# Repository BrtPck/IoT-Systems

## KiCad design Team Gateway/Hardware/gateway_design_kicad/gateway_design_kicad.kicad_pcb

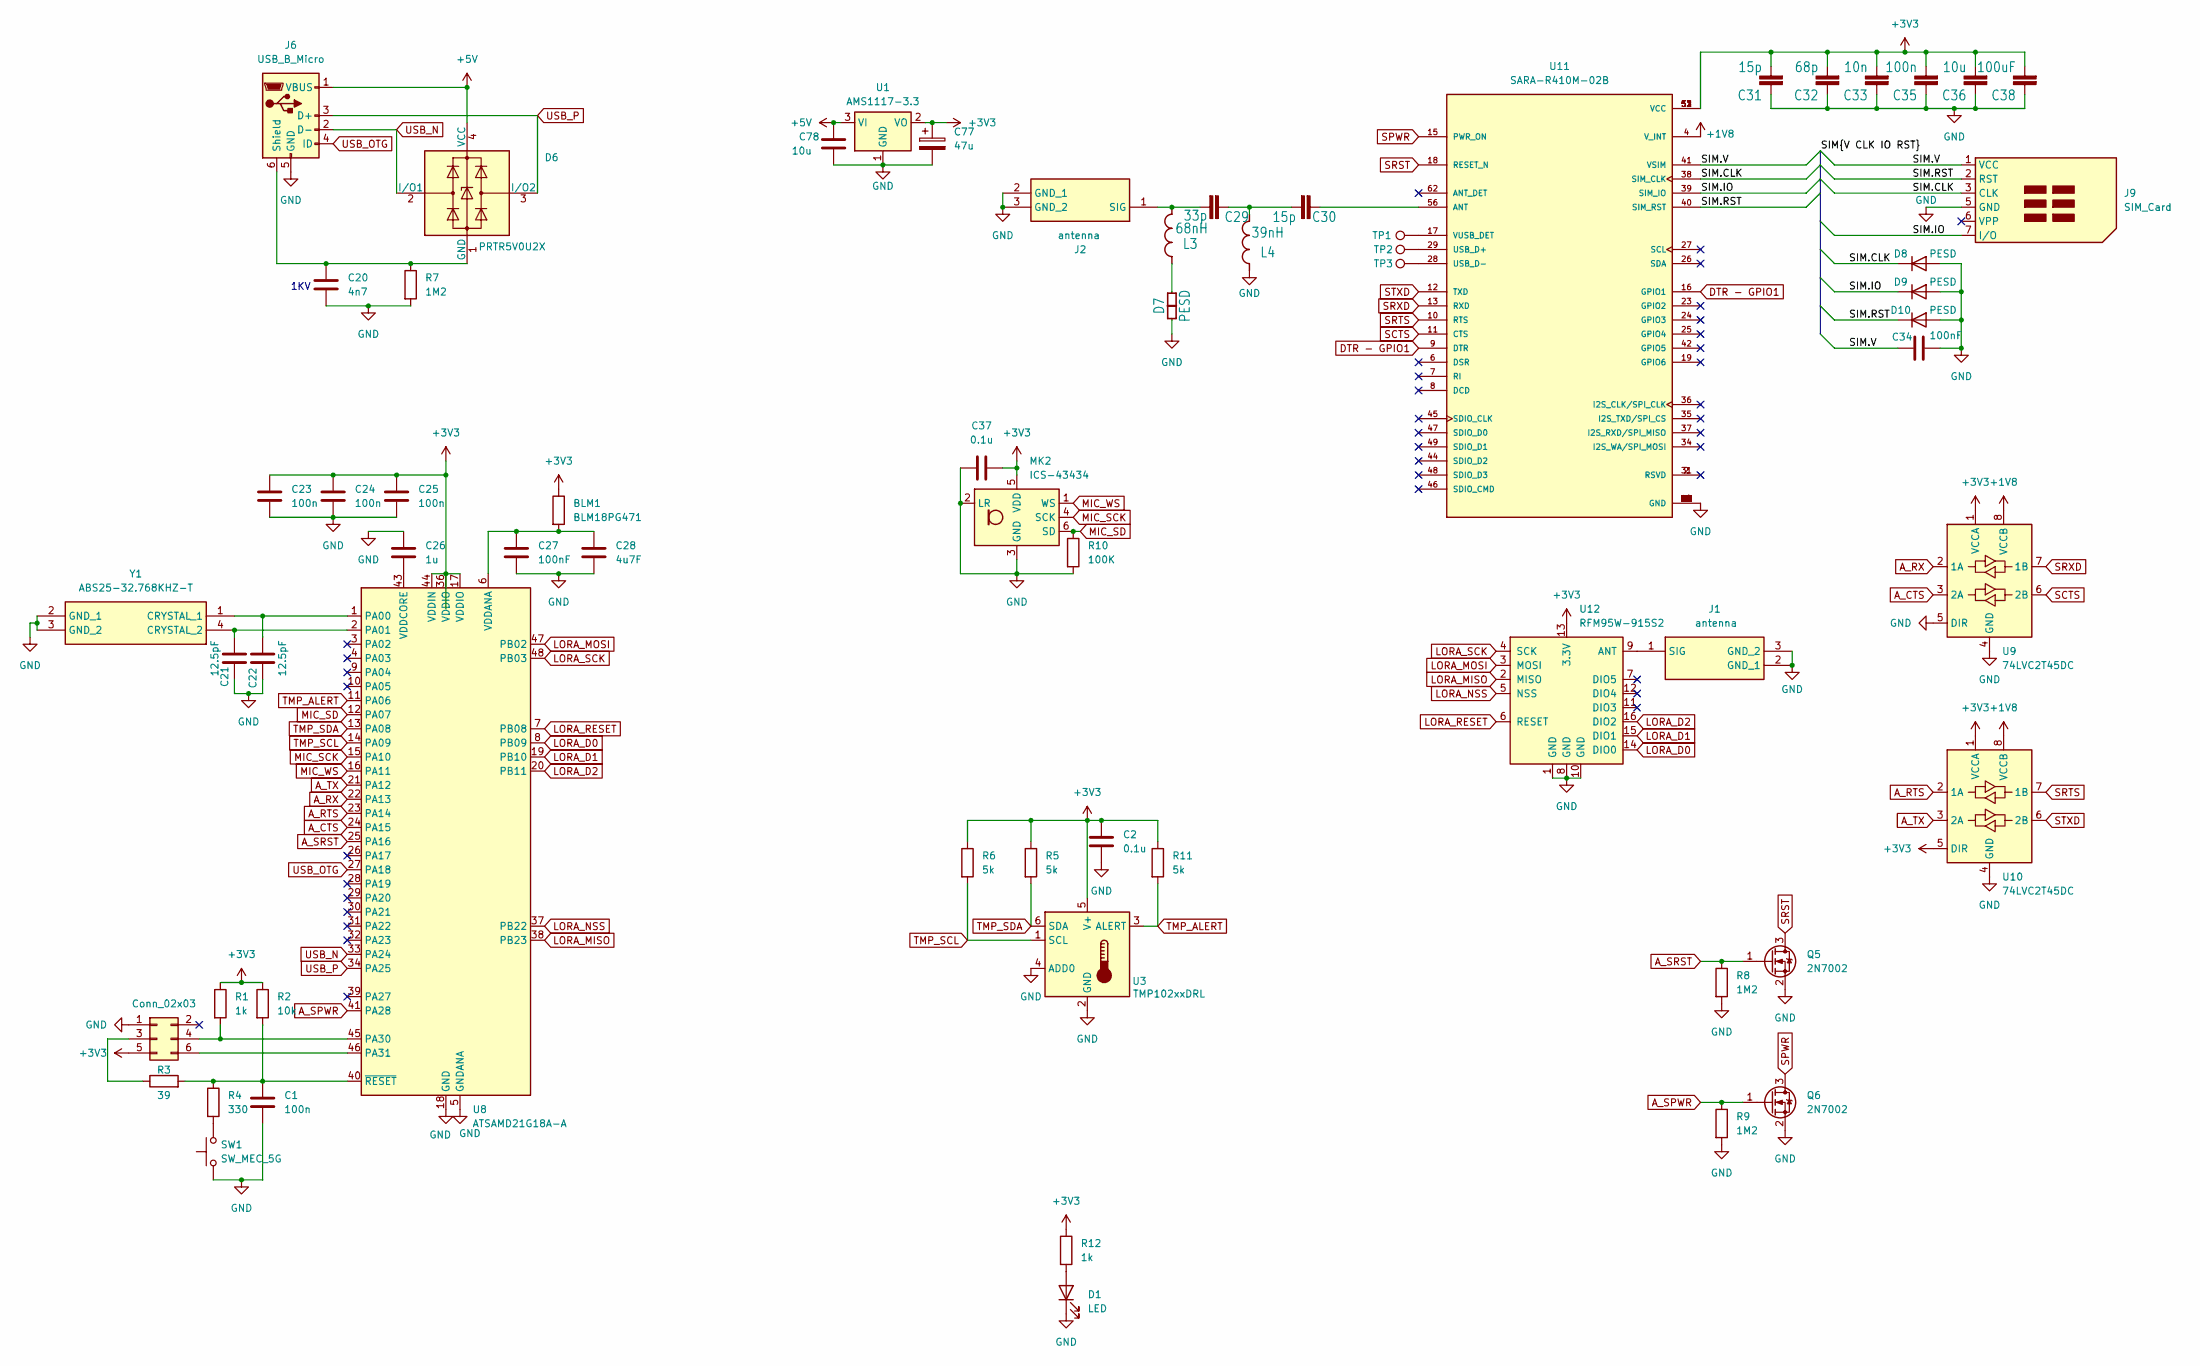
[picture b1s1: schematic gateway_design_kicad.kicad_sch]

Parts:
BLM1: BLM18PG471; C_0603_1608Metric_Pad1.08x0.95mm_HandSolder
C1, C23, C24, C25, C35: 100n; C_0805_2012Metric_Pad1.18x1.45mm_HandSolder
C2, C37: 0.1u; C_0805_2012Metric_Pad1.18x1.45mm_HandSolder
C20: 4n7; C_0805_2012Metric_Pad1.18x1.45mm_HandSolder
C21, C22: 12.5pF; C_0805_2012Metric_Pad1.18x1.45mm_HandSolder
C26: 1u; C_0805_2012Metric_Pad1.18x1.45mm_HandSolder
C27, C34: 100nF; C_0805_2012Metric_Pad1.18x1.45mm_HandSolder
C28: 4u7F; C_0805_2012Metric_Pad1.18x1.45mm_HandSolder
C29: 33p; C_0805_2012Metric_Pad1.18x1.45mm_HandSolder
C30, C31: 15p; C_0805_2012Metric_Pad1.18x1.45mm_HandSolder
C32: 68p; C_0805_2012Metric_Pad1.18x1.45mm_HandSolder
C33: 10n; C_0805_2012Metric_Pad1.18x1.45mm_HandSolder
C36, C78: 10u; C_0805_2012Metric_Pad1.18x1.45mm_HandSolder
C38: 100uF; C_0805_2012Metric_Pad1.18x1.45mm_HandSolder
C77: 47u; C_0805_2012Metric_Pad1.18x1.45mm_HandSolder
D1: LED; LED_0805_2012Metric_Pad1.15x1.40mm_HandSolder
D6: PRTR5V0U2X; SOT-143
D7, D8, D9, D10: PESD; eigen_PESD0402-140
J1, J2: antenna; Antenna; Mouser Part Number N/A
J6: USB_B_Micro; 21344412
J7: Conn_02x03; PinHeader_2x03_P2.54mm_Vertical
J9: SIM_Card; SIM5051601800A
L3: 68nH; C_0805_2012Metric_Pad1.18x1.45mm_HandSolder
L4: 39nH; C_0603_1608Metric_Pad1.08x0.95mm_HandSolder
MK2: ICS-43434; InvenSense_ICS-43434-6_3.5x2.65mm
Q5, Q6: 2N7002; SOT-23
R1, R12: 1k; R_0805_2012Metric_Pad1.20x1.40mm_HandSolder
R2: 10k; R_0805_2012Metric_Pad1.20x1.40mm_HandSolder
R3: 39; R_0805_2012Metric_Pad1.20x1.40mm_HandSolder
R4: 330; R_0805_2012Metric_Pad1.20x1.40mm_HandSolder
R5, R6, R11: 5k; R_0805_2012Metric_Pad1.20x1.40mm_HandSolder
R7, R8, R9: 1M2; R_0805_2012Metric_Pad1.20x1.40mm_HandSolder
R10: 100K; R_0805_2012Metric_Pad1.20x1.40mm_HandSolder
SW1: SW_MEC_5G; SW_DIP_SPSTx01_Slide_6.7x4.1mm_W6.73mm_P2.54mm_LowProfile_J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
TP1, TP2, TP3: TestPoint; TestPoint_Pad_2.0x2.0mm
U1: AMS1117-3.3; SOT-223-3_TabPin2
U3: TMP102xxDRL; SOT-563
U8: ATSAMD21G18A-A; TQFP-48_7x7mm_P0.5mm
U9, U10: 74LVC2T45DC; VSSOP-8_2.3x2mm_P0.5mm
U11: SARA-R410M-02B; XCVR_SARA-R410M-02B; PARTREV R20
U12: RFM95W-915S2; XCVR_RFM95W-915S2
Y1: ABS25-32.768KHZ-T; ABS2532768KHZT; Manufacturer_Part_Number ABS25-32.768KHZ-T; Mouser Part Number 815-ABS25-32.768KHZT

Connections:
+1V8: U9.8 (VCCB), U10.8 (VCCB), U11.4 (V_INT)
+3V3: BLM1.1, C2.1, C23.1, C24.1, C25.1, C31.2, C32.2, C33.2, C35.2, C36.2, C37.2, C38.2, C77.1, J7.5, MK2.5 (VDD), R1.1, R2.1, R5.1, R6.1, R11.1, R12.1, U1.2 (VO), U3.5 (V+), U8.17 (VDDIO), U8.36 (VDDIO), U8.44 (VDDIN), U9.1 (VCCA), U10.1 (VCCA), U10.5 (DIR), U11.51 (VCC), U11.52 (VCC), U11.53 (VCC), U12.13 (3.3V)
+5V: C78.1, D6.4 (VCC), J6.1 (VBUS), U1.3 (VI)
/SIM.CLK: D8.1 (K), J9.3 (CLK), U11.38 (SIM_CLK)
/SIM.IO: D9.1 (K), J9.7 (I/O), U11.39 (SIM_IO)
/SIM.RST: D10.1 (K), J9.2 (RST), U11.40 (SIM_RST)
/SIM.V: C34.1, J9.1 (VCC), U11.41 (VSIM)
A_CTS: U8.24 (PA15), U9.3 (2A)
A_RTS: U8.23 (PA14), U10.2 (1A)
A_RX: U8.22 (PA13), U9.2 (1A)
A_SPWR: Q6.1 (G), R9.1, U8.41 (PA28)
A_SRST: Q5.1 (G), R8.1, U8.25 (PA16)
A_TX: U8.21 (PA12), U10.3 (2A)
DTR - GPIO1: U11.9 (DTR), U11.16 (GPIO1)
GND: C1.2, C2.2, C20.2, C21.1, C22.1, C23.2, C24.2, C25.2, C26.1, C27.2, C28.2, C31.1, C32.1, C33.1, C34.2, C35.1, C36.1, C37.1, C38.1, C77.2, C78.2, D1.1 (K), D7.1, D8.2 (A), D9.2 (A), D10.2 (A), J1.2 (GND_1), J1.3 (GND_2), J2.2 (GND_1), J2.3 (GND_2), J6.5 (GND), J7.1, J9.5 (GND), L4.1, MK2.2 (LR), MK2.3 (GND), Q5.2 (S), Q6.2 (S), R7.2, R8.2, R9.2, R10.2, SW1.1 (A), U1.1 (GND), U3.2 (GND), U3.4 (ADD0), U8.5 (GNDANA), U8.18 (GND), U8.35 (GND), U8.42 (GND), U9.4 (GND), U9.5 (DIR), U10.4 (GND), U11.1 (GND), U11.3 (GND), U11.5 (GND), U11.14 (GND), U11.20 (GND), U11.21 (GND), U11.22 (GND), U11.30 (GND), U11.32 (GND), U11.33 (GND), U11.43 (GND), U11.50 (GND), U11.54 (GND), U11.55 (GND), U11.57 (GND), U11.58 (GND), U11.59 (GND), U11.60 (GND), U11.61 (GND), U11.63 (GND), U11.64 (GND), U11.65 (GND), U11.66 (GND), U11.67 (GND), U11.68 (GND), U11.69 (GND), U11.70 (GND), U11.71 (GND), U11.72 (GND), U11.73 (GND), U11.74 (GND), U11.75 (GND), U11.76 (GND), U11.77 (GND), U11.78 (GND), U11.79 (GND), U11.80 (GND), U11.81 (GND), U11.82 (GND), U11.83 (GND), U11.84 (GND), U11.85 (GND), U11.86 (GND), U11.87 (GND), U11.88 (GND), U11.89 (GND), U11.90 (GND), U11.91 (GND), U11.92 (GND), U11.93 (GND), U11.94 (GND), U11.95 (GND), U11.96 (GND), U12.1 (GND), U12.8 (GND), U12.10 (GND), Y1.2 (GND_1), Y1.3 (GND_2); also elsewhere on the board
LORA_D0: U8.8 (PB09), U12.14 (DIO0)
LORA_D1: U8.19 (PB10), U12.15 (DIO1)
LORA_D2: U8.20 (PB11), U12.16 (DIO2)
LORA_MISO: U8.38 (PB23), U12.2 (MISO)
LORA_MOSI: U8.47 (PB02), U12.3 (MOSI)
LORA_NSS: U8.37 (PB22), U12.5 (NSS)
LORA_RESET: U8.7 (PB08), U12.6 (RESET)
LORA_SCK: U8.48 (PB03), U12.4 (SCK)
MIC_SCK: MK2.4 (SCK), U8.15 (PA10)
MIC_SD: MK2.6 (SD), R10.1, U8.12 (PA07)
MIC_WS: MK2.1 (WS), U8.16 (PA11)
unnamed: C29.1, C30.2, L4.2
unnamed: D1.2 (A), R12.2
unnamed: C20.1, D6.1 (GND), J6.6 (Shield), R7.1
unnamed: D7.2, L3.1
unnamed: J1.1 (SIG), U12.9 (ANT)
unnamed: C29.2, J2.1 (SIG), L3.2
unnamed: J7.3, R3.1
unnamed: J7.4, R1.2, U8.45 (PA30)
unnamed: J7.6, U8.46 (PA31)
unnamed 35: R4.2, SW1.2 (B); also elsewhere on the board
unnamed: C22.2, U8.1 (PA00), Y1.1 (CRYSTAL_1)
unnamed: C21.2, U8.2 (PA01), Y1.4 (CRYSTAL_2)
unnamed: BLM1.2, C27.1, C28.1, U8.6 (VDDANA)
unnamed: C26.2, U8.43 (VDDCORE)
unnamed: C1.1, R2.2, R3.2, R4.1, U8.40 (~RESET)
unnamed: C30.1, U11.56 (ANT)
unnamed 42: TP2.1, U11.29 (USB_D+); also elsewhere on the board
unnamed 43: TP3.1, U11.28 (USB_D-); also elsewhere on the board
unnamed: TP1.1, U11.17 (VUSB_DET)
SCTS: U9.6 (2B), U11.11 (CTS)
SPWR: Q6.3 (D), U11.15 (PWR_ON)
SRST: Q5.3 (D), U11.18 (RESET_N)
SRTS: U10.7 (1B), U11.10 (RTS)
SRXD: U9.7 (1B), U11.13 (RXD)
STXD: U10.6 (2B), U11.12 (TXD)
TMP_ALERT: R11.2, U3.3 (ALERT), U8.11 (PA06)
TMP_SCL: R6.2, U3.1 (SCL), U8.14 (PA09)
TMP_SDA: R5.2, U3.6 (SDA), U8.13 (PA08)
USB_N: D6.2 (I/O1), J6.2 (D-), U8.33 (PA24)
USB_OTG: J6.4 (ID), U8.27 (PA18)
USB_P: D6.3 (I/O2), J6.3 (D+), U8.34 (PA25)

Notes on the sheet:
1KV

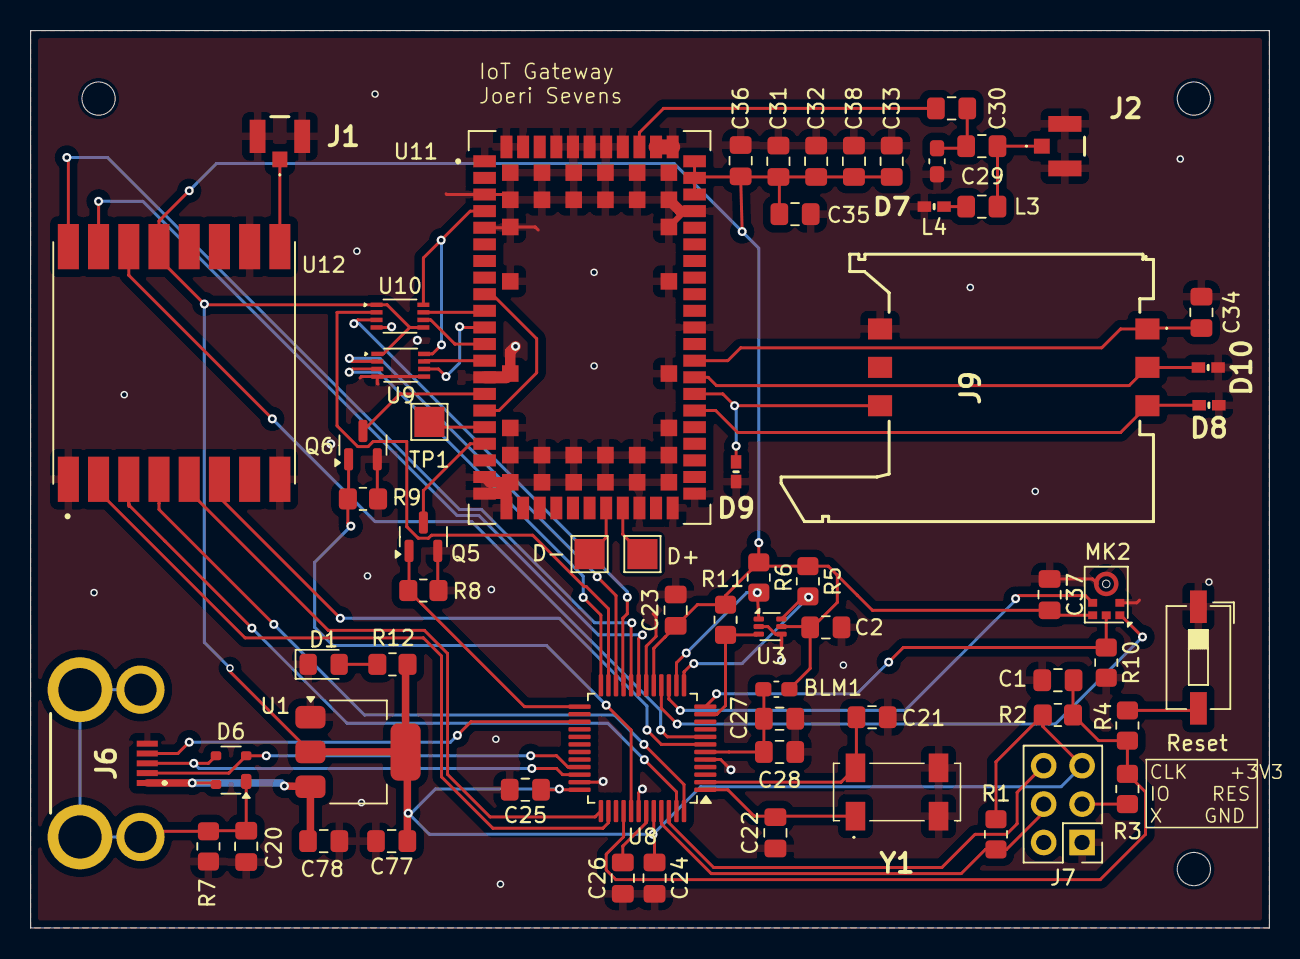
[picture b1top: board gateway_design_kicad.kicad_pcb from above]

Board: 2 copper layers, 82.0 x 59.4 mm, 64 parts (0 on the bottom side), 57 nets.

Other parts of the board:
D+: TestPoint; TestPoint_Pad_2.0x2.0mm
D-: TestPoint; TestPoint_Pad_2.0x2.0mm
Reset: SW_MEC_5G; SW_DIP_SPSTx01_Slide_6.7x4.1mm_W6.73mm_P2.54mm_LowProfile_J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

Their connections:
GND: Reset.1 (A); also elsewhere on the board
unnamed 35: Reset.2 (B); also elsewhere on the board
unnamed 42: D+.1; also elsewhere on the board
unnamed 43: D-.1; also elsewhere on the board

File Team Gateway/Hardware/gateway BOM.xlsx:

Reference | Value | Datasheet | Footprint | Qty | DNP
BLM1 | BLM18PG471 | ~ | Capacitor_SMD:C_0603_1608Metric_Pad1.08x0.95mm_HandSolder | 1
C1,C23,C24,C25,C35 | 100n | -- gemengde waarden -- | Capacitor_SMD:C_0805_2012Metric_Pad1.18x1.45mm_HandSolder | 5
C2,C37 | 0.1u | ~ | Capacitor_SMD:C_0805_2012Metric_Pad1.18x1.45mm_HandSolder | 2
C20 | 4n7 | ~ | Capacitor_SMD:C_0805_2012Metric_Pad1.18x1.45mm_HandSolder | 1
C21,C22 | 12.5pF | ~ | Capacitor_SMD:C_0805_2012Metric_Pad1.18x1.45mm_HandSolder | 2
C26 | 1u | ~ | Capacitor_SMD:C_0805_2012Metric_Pad1.18x1.45mm_HandSolder | 1
C27,C34 | 100nF | ~ | Capacitor_SMD:C_0805_2012Metric_Pad1.18x1.45mm_HandSolder | 2
C28 | 4u7F | ~ | Capacitor_SMD:C_0805_2012Metric_Pad1.18x1.45mm_HandSolder | 1
C29 | 33p |  | Capacitor_SMD:C_0805_2012Metric_Pad1.18x1.45mm_HandSolder | 1
C30,C31 | 15p |  | Capacitor_SMD:C_0805_2012Metric_Pad1.18x1.45mm_HandSolder | 2
C32 | 68p |  | Capacitor_SMD:C_0805_2012Metric_Pad1.18x1.45mm_HandSolder | 1
C33 | 10n |  | Capacitor_SMD:C_0805_2012Metric_Pad1.18x1.45mm_HandSolder | 1
C36,C78 | 10u | -- gemengde waarden -- | Capacitor_SMD:C_0805_2012Metric_Pad1.18x1.45mm_HandSolder | 2
C38 | 100uF |  | Capacitor_SMD:C_0805_2012Metric_Pad1.18x1.45mm_HandSolder | 1
C77 | 47u | ~ | Capacitor_SMD:C_0805_2012Metric_Pad1.18x1.45mm_HandSolder | 1
D1 | LED | ~ | LED_SMD:LED_0805_2012Metric_Pad1.15x1.40mm_HandSolder | 1
D6 | PRTR5V0U2X | https://assets.nexperia.com/documents/data-sheet/PRTR5V0U2X.pdf | Package_TO_SOT_SMD:SOT-143 | 1
D7,D8,D9,D10 | PESD | -- gemengde waarden -- | Library:eigen_PESD0402-140 | 4
J1,J2 | antenna |  | Library:Antenna | 2
J6 | USB_B_Micro | ~ | Library:21344412 | 1
J7 | Conn_02x03 | ~ | Connector_PinHeader_2.54mm:PinHeader_2x03_P2.54mm_Vertical | 1
J9 | SIM_Card | ~ | Library:SIM5051601800A | 1
L3 | 68nH |  | Capacitor_SMD:C_0805_2012Metric_Pad1.18x1.45mm_HandSolder | 1
L4 | 39nH |  | Capacitor_SMD:C_0603_1608Metric_Pad1.08x0.95mm_HandSolder | 1
MK2 | ICS-43434 | https://www.invensense.com/wp-content/uploads/2016/02/DS-000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 | Sensor_Audio:InvenSense_ICS-43434-6_3.5x2.65mm | 1
Q5,Q6 | 2N7002 | https://www.onsemi.com/pub/Collateral/NDS7002A-D.PDF | Package_TO_SOT_SMD:SOT-23 | 2
R1,R12 | 1k | ~ | Resistor_SMD:R_0805_2012Metric_Pad1.20x1.40mm_HandSolder | 2
R2 | 10k | ~ | Resistor_SMD:R_0805_2012Metric_Pad1.20x1.40mm_HandSolder | 1
R3 | 39 | ~ | Resistor_SMD:R_0805_2012Metric_Pad1.20x1.40mm_HandSolder | 1
R4 | 330 | ~ | Resistor_SMD:R_0805_2012Metric_Pad1.20x1.40mm_HandSolder | 1
R5,R6,R11 | 5k | ~ | Resistor_SMD:R_0805_2012Metric_Pad1.20x1.40mm_HandSolder | 3
R7,R8,R9 | 1M2 | ~ | Resistor_SMD:R_0805_2012Metric_Pad1.20x1.40mm_HandSolder | 3
R10 | 100K | ~ | Resistor_SMD:R_0805_2012Metric_Pad1.20x1.40mm_HandSolder | 1
SW1 | SW_MEC_5G | http://www.apem.com/int/index.php?controller=attachment&id_a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 | Button_Switch_SMD:SW_DIP_SPSTx01_Slide_6.7x4.1mm_W6.73mm_P2.54mm_LowProfile_JPin | 1
TP1,TP2,TP3 | TestPoint | ~ | TestPoint:TestPoint_Pad_2.0x2.0mm | 3
U1 | AMS1117-3.3 | http://www.advanced-monolithic.com/pdf/ds1117.pdf | Package_TO_SOT_SMD:SOT-223-3_TabPin2 | 1
U3 | TMP102xxDRL | https://www.ti.com/lit/ds/symlink/tmp102.pdf | Package_TO_SOT_SMD:SOT-563 | 1
U8 | ATSAMD21G18A-A | http://ww1.microchip.com/downloads/en/DeviceDoc/SAM_D21_DA1_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 | Package_QFP:TQFP-48_7x7mm_P0.5mm | 1
U9,U10 | 74LVC2T45DC | https://assets.nexperia.com/documents/data-sheet/74LVC_LVCH2T45.pdf | Package_SO:VSSOP-8_2.3x2mm_P0.5mm | 2
U11 | SARA-R410M-02B |  | Library:XCVR_SARA-R410M-02B | 1
U12 | RFM95W-915S2 | https://www.hoperf.com/data/upload/portal/20181127/5bfcbea20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 | Library:XCVR_RFM95W-915S2 | 1
Y1 | ABS25-32.768KHZ-T | https://abracon.com/Resonators/abs25.pdf | Library:ABS2532768KHZT | 1

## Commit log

2024-12-18 Create test
2024-12-18 Delete test
    delete test files
2024-12-18 Create datalayout
2024-12-18 update hardware files NODE
2024-12-18 Added files from team Posture
2024-12-18 kicad gateway
2024-12-19 Add files via upload
    add node code, lora library changes and heartrate debugger
2024-12-19 Rename main.cpp to nodeCode.cpp
